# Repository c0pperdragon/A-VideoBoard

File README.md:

# A-Video Board

A small FPGA board with a component video interface to directly drive
an analog monitor or TV input.
Its main purpose is to create component video / RGB mods of vintage
home computers and consoles or to provide video output for hobby projects.

It consists of the purest minimum parts necessary to have a multi-purpose
FPGA combined with a simple way to generate a YPbPr signal. After much research
I finally settled on a cheap MAX 10 device in a TQFP-144 package which I can 
solder by hand (barely). The rest of the parts are pretty cheap and quite easy to solder. 

To interface any of the vintage systems to the A-Video Board, level shifters
are necessary to translate the 5 volt to 3.3 volt for the FPGA input pins. These level
shifters can be implemented in a system specific daughter board that can be stacked
on top of the A-Video board. Any such interface board can probably be implemented in a 
simple single-sided wide-pitch PCB that can be even home-etched with some experience.

Currently I have built applications of the A-Video board for 
* [Commodore 64](/c64mod)
* [Atari 8 bit machines](/atarimod)
* [ZX Spectrum](/zxspectrummod)

## Images

## Board design

The board has these main parts

* 10M02SCE144: fairly cheap FPGA of the MAX10 series
* LM1117IMPX-3.3:   linear voltage regulator
* LFSPX0024957:     25Mhz clock generator
* THS7316:          video output amplifier
* R1-R19:           three 5-bit DACs made from transistors

and various supporting passive components, mainly decoupling, filtering and pull-ups.

It has the following connectors:
* GPIO1  20-pin header that directly connects to FPGA pins
* GPIO2  10-pin header with two pins providing GND and +3.3V, the remaining 8 connect to the FPGA.
* JTAG   10-pin header for programming the FPGA (via an USB-Blaster or compatible device)
* 3 RCA sockets to output the video signal (normally YPbPr, but other formats could be produced as well).
 Note that in the schematics these sockets are denoted as BNC, but are actually RCA connectors of type 
 RCJ-046 (green), RCJ-042 (red), RCJ-045 (blue).
* GND, VIN  Provide between 4.5V and 9V as supply voltage. The board consumes about 80mA.
 
## Contact
If you plan to use an A-Video board, feel free to contact me for assistance:
reinhard.grafl (at) aon.at  
Maybe I will either have some spare PCBs I could send you to populate yourself,
or even provide you with a fully assembled board for the cost of the parts and shipping.

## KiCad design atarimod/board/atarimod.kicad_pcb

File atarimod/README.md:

# Atari RGB Mod

Built on the A-Video board, this is a modification usable for Atari 8-bit 
computers that generate YPbPr signal in either 288p or 576p to display on
modern displays. 

## Motivation

These old Atari computers generate the colour output signal directly in the weird way that was
necessary to construct a PAL or NTSC signal. The technique is called "quadrature amplitude modulation" and has the
disadvantage of not being completely reversible, so the original colours can not be reconstructed from this
signal.
Even worse, the XL line of machines does not even provide this signal directly on the video output, but
only already combined with the luminance signal as composite video. There are simple ways to provide 
separate luminance and colour, but even then the quality is pretty bad. 
This was not such a problem on cathode ray tube (CRT) displays, but on modern LCD TVs this signal looks totally
unusable.

So, no matter how I tried, I could not reliably re-construct the original colours from the colour signal output. 
The only way to really solve the issue was to intercept the necessary information in digital form to 
create a perfectly sharp and clear analog video signal by my own circuitry. 

## Theory of Operation

The FPGA chip passively listens to all relevant pins of the GTIA graphics chip and re-implements the 
relevant logic of the GTIA in its logic fabric, effectively providing a second GTIA (parts of it).
To sniff the signals from the GTIA, a specific adapter board is needed that sits between the 
GTIA and its socket. Revision 3 of the adapter is now pretty small and should fit in all Atari models.
From this adapter, a 20-pin ribbon cable (either mounted permanently to the adapter or using a plug)
leads to the FPGA board.
This FPGA board can either be the generic A-Video board or a re-purposed C64 Video Enhancement Board. 
Both boards are firmeware-compatible, but differ in their size and connector options. You should 
also be able to fairly easily change these connectivity options anyway.

## Adapter building details (Rev. 3)

In the doc folder, there are schematics, gerber files and a bill of material to build the adapter.
Ideally you need a 0.8mm PCB (a slighly thicker boards will also work) and assemble everything except
the P1 socket.  This specific socket is meant to be put into the big holes, so the extra-long solder tails 
will stick out pretty far on the bottom side. These will then fit into the IC socket on the Atari.
Take care not to get any solder onto these thin tails when soldering the ticker barrels into the 
adapter board (this can become tricky, but with a 0.8mm board it should not be too hard).
Before actually soldering the socket you have to cut away one of the plastic cross-beams so it
will not conflict with the ICs.

For attaching the 20-pin ribbon cable to P2, you have several options. I used an angled 
pin-header with a standard ribbon cable connector to keep a low profile. If there is space 
in your device you can as well use a straight pain-header. An even more sophisticated option
is a permantent PCB-to-ribbon-cable header which can be found with quite a low profile.
You can even solder the ribbon cable wires direcly into the board or whatever you fancy.

## FPGA Details

The FPGA on the A-Video board is programmed in VHDL, using the free version of the Quartus II development suite.
This chip has an on-board non-volatile program memory, so no external flash is needed and the chip has
a very short start-up time. There is a PLL built in which I use to generate a 228Mhz clock from the 25Mhz reference.
With this 228Mhz and some advanced  programming I can multiply the Atari pixel clock to a pretty clean (below 1 ns jitter) 14,1875 MHz clock to drive the whole circuit and create a nice output signal.

On non-PAL machines the Atari pixel clock runs at a slightly different speed. There the clock multiplier circuit will actually produce an internal clock that has variations in their clock cycle length. This will lead
to a slightly different length of every other pixel in 240p mode, and of every 4th pixel in 480p mode.

## Output

The mod can be used to create three different output formats:
* 240p/288p  (default)
* 480p/576p
* 480p/576p with scanline effect 

Selecting the output can be done by jumper connectors or an external switch (already provided 
in the C64 Video Enhancement):
* Connect GPIO2_4 to GND: 480p/576p
* Connect GPIO2_5 or GPIO2_6 to GND: 480p/576p with scanline effect

## Images
")

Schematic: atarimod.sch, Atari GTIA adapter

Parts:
C1, C2: 10uF; C_0805_2012Metric_Pad1.15x1.40mm_HandSolder
C3, C4, C5, C6: 100nF; C_0603_1608Metric_Pad1.05x0.95mm_HandSolder
IC1, IC2, IC3, IC4: SN74LVC14ADBR; SSOP-14_5.3x6.2mm_P0.65mm
P1: DIP40_Socket; socket_embedded_40pin
P2: CONN_02X10; PinHeader_2x10_P2.54mm_Vertical
R10: 100; R_0805_2012Metric_Pad1.15x1.40mm_HandSolder
U2: MIC5504-3.3YM5; SOT-23-5

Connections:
+3V3: C2.1, C3.2, C4.2, C5.2, C6.2, IC1.14, IC2.14, IC3.14, IC4.14, U2.5
+5V: C1.1, P1.27, U2.1, U2.3
A0: IC1.4, P2.3
A1: IC1.2, P2.1
A2: IC1.12, P2.2
A3: IC1.10, P2.4
A4: IC1.8, P2.6
AN0: IC4.2, P2.13
AN1: IC4.4, P2.15
AN2: IC4.6, P2.17
CLK: IC4.12, R10.2
CS: IC3.8, P2.18
D0: IC3.2, P2.11
D1: IC2.6, P2.9
D2: IC2.4, P2.7
D3: IC2.2, P2.5
D4: IC2.12, P2.8
D5: IC2.10, P2.10
D6: IC2.8, P2.12
D7: IC3.12, P2.14
GND: C1.2, C2.2, C3.1, C4.1, C5.1, C6.1, IC1.5, IC1.7, IC2.7, IC3.3, IC3.5, IC3.7, IC4.7, IC4.9, P1.3, U2.2
HALT: IC4.10, P2.20
unnamed: IC1.1, P1.1
unnamed: IC1.3, P1.2
unnamed: IC1.9, P1.38
unnamed: IC1.11, P1.39
unnamed: IC1.13, P1.40
unnamed: IC2.1, P1.4
unnamed: IC2.3, P1.5
unnamed: IC2.5, P1.6
unnamed: IC2.9, P1.35
unnamed: IC2.11, P1.36
unnamed: IC2.13, P1.37
unnamed: IC3.1, P1.7
unnamed: IC3.9, P1.32
unnamed: IC3.11, P1.33
unnamed: IC3.13, P1.34
unnamed: IC4.1, P1.18
unnamed: IC4.3, P1.19
unnamed: IC4.5, P1.20
unnamed: IC4.11, P1.26
unnamed: IC4.13, P1.29
unnamed: P2.19, R10.1
RW: IC3.10, P2.16

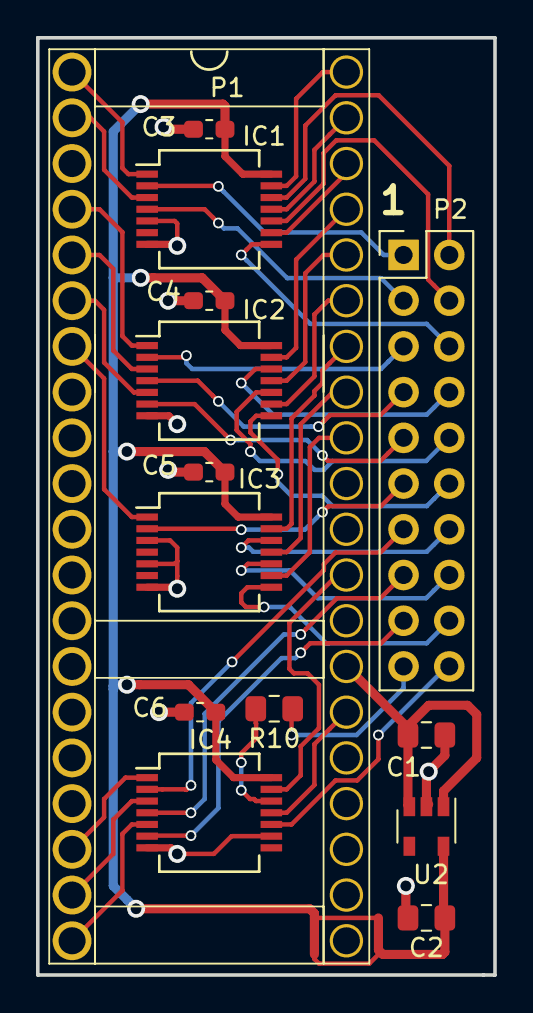
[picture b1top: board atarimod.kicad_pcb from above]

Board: 2 copper layers, 25.4 x 52.1 mm, 14 parts (0 on the bottom side), 44 nets.

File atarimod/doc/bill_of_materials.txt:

References       Type                                                 Value/Part Number      Size

C1,C2            Ceramic Capacitor                                    1 uF                   2012 metric
C3,C4,C5,C6      Ceramic Capacitor                                    100 nF                 1608 metric
IC1,IC2,IC3,IC4  Schmitt-Trigger Inverter                             SN74LVC14ADBR          SSOP-14
P1               40-pin IC precision socket with long solder tails    111-93-640-41-001000   DIP 40
P2               Pinheader/Ribbon cable connector                     any                    2x20, 2.54mm 
R10              SMD Resistor                                         100 ohm                2012 metric
U2               LDO Voltage Regulator 3.3V                           MIC5504-3.3YM5         SOT-23-5

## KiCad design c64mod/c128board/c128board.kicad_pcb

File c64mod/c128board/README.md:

# C128 adapter

This is an adapater to be plugged between the VIC-IIe and its socket in a Commodore 128.
Using this the, C64 Video Enchancement Board should in theory be able to work for the 40 columns mode 
display of the C128.

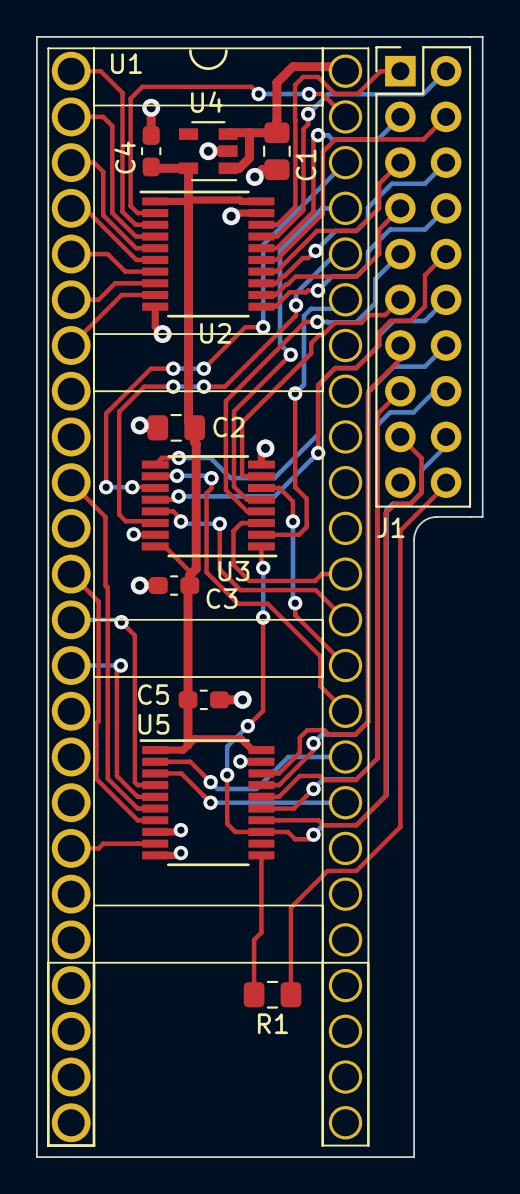
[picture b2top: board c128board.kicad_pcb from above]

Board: 2 copper layers, 24.8 x 62.2 mm, 12 parts (0 on the bottom side), 46 nets.

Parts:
C1, C2: 10uF; C_0805_2012Metric_Pad1.15x1.40mm_HandSolder
C3, C4, C5: 100nF; C_0603_1608Metric_Pad1.05x0.95mm_HandSolder
J1: Conn_02x10_Odd_Even; PinHeader_2x10_P2.54mm_Vertical
R1: 100Ohm; R_0805_2012Metric_Pad1.15x1.40mm_HandSolder
U1: VIC-IIe; socket_embedded_48pin
U2: MIC5504-3.3YM5; SOT-23-5
U3: LVC257; TSSOP-16_4.4x5mm_P0.65mm
U4, U5: LVC245; TSSOP-20_4.4x6.5mm_P0.65mm

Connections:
+3V3: C2.1, C3.1, C4.1, C5.1, U2.5, U3.16, U4.1, U4.20, U5.1, U5.20
+5V: C1.1, U1.48, U2.1, U2.3
A0: J1.14, U5.17
A1: J1.13, U5.18
AEC: J1.18, U3.1, U5.13
BA: J1.17, U5.14
CS: J1.15, U5.16
DB0: J1.8, U4.11
DB1: J1.7, U4.12
DB2: J1.6, U4.13
DB3: J1.5, U4.14
DB4: J1.4, U4.15
DB5: J1.3, U4.16
DB6: J1.2, U4.17
DB7: J1.1, U4.18
DB8_A2: J1.12, U3.9
DB9_A3: J1.11, U3.7
DB10_A4: J1.10, U3.12
DB11_A5: J1.9, U3.4
GND: C1.2, C2.2, C3.2, C4.2, C5.2, J1.19, U1.24, U2.2, U3.8, U3.15, U4.10, U4.19, U5.8, U5.10, U5.19
unnamed: R1.2, U5.11
unnamed: U1.1, U4.3
unnamed: U1.2, U4.4
unnamed: U1.3, U4.5
unnamed: U1.4, U4.6
unnamed: U1.5, U4.7
unnamed: U1.6, U4.8
unnamed: U1.7, U4.9
unnamed: U1.10, U5.6
unnamed: U1.12, U5.7
unnamed: U1.13, U5.4
unnamed: U1.14, U5.5
unnamed: U1.18, U5.9
unnamed: U1.32, U5.3
unnamed: U1.33, U5.2
unnamed: U1.34, U3.10
unnamed: U1.35, U3.6
unnamed: U1.36, U3.13
unnamed: U1.37, U3.3
unnamed: U1.43, U3.2
unnamed: U1.44, U3.14
unnamed: U1.45, U3.5
unnamed: U1.46, U3.11
unnamed: U1.47, U4.2
PHI0: J1.20, R1.1
RW: J1.16, U5.15

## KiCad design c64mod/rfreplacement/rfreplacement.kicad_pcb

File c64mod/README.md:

# C64 RGB Mod

Built on the A-Video board, this is a modification usable for the Commodore 64 computer
that generates a YPbPr signal in either 288p or 576p to display on modern displays.

## Motivation

I wanted to get the most perfect display from an original C64 computer. After many failed attempts to 
reconstruct a digitally perfect pixel-by-pixel display from the S-Video output, I finally came back
to my original idea to emulate the inner workings of the VIC-II chip. 
So, as for the atari 8-bit line and the ZX Spectrum, I applied my trusty A-Video board. 

## Building details

The FPGA chip passively listens to all relevant pins of the VIC graphics chip and re-implements the 
relevant logic of the GTIA in its logic fabric, effectively providing a second VIC (parts of it).
The mod board consists of two parts: A small adapter board that sits under the VIC and sniffs all relevant
pins, and the A-Video board that does the actual processing. The 5 volt signals from the C64 are
level-shifted by the adapter board down to 3.3 volts for use by the FPGA.
Since the adapter board only listens to the signals (with very high-impedience input pins), it 
will not influence the working of the VIC or any other part of the system in any way. The FPGA implementation
may have some glitches, but this should only affect the visual output.
Note that the mod consumes an additional 100mA of current from the 5 volt rail, 
so make sure that your power supply can handle this.

## Assembling the VIC adapter board

If you want to build your own adapter board, you need to have a PCB manufactured with 0.8mm thickness 
(use the gerber.zip for ordering). After soldering the ICs and passives, you need to fit a 40-pin
IC socket into the big holes. Use the socket type with round pins (the more expensive ones).
Solder from below and remove as much excess solder as possible. Then install the ribbon cable connector.
Take special care when installing the voltage regulator, as this small package always gave me the most trouble.
For your convenience, I have set up a [BOM](doc/adapterboard_bom.ods) and a parts list at 
[mouser](https://www.mouser.com/ProjectManager/ProjectDetail.aspx?AccessID=2b75b16750)
containing everything to build the board.

## Connectors

In my current build, the A-Video port is just screwed on top of the existing RF modulator.
This saved me the trouble of removing the modulator first (which would need additional circuitry to
keep the A/V output working). But this comes at the cost that the back of the computer case 
now has a rather large and ugly hole. I am pretty sure there are good solutions available to get rid of
this big modulator box while keeping the A/V functionality. Then the YPbPr connectors would be located
much lower and would look more natural.
If you even want a totally reversible mod you could probably place the A-Video board somewhere inside the
case and bring out the YPbPr cable through the user port opening.

## Output

The mod can be used to create three different output formats:
* 288p (default)
* 576p
* 576p with scanline effect

Selecting the output can be done by jumper connectors or an external switch:
* Connect GPIO2_4 to GPIO2_2 (GND): 576p
* Connect GPIO2_6 to GPIO2_2 (GND): 576p with scanline effect

## Images

")

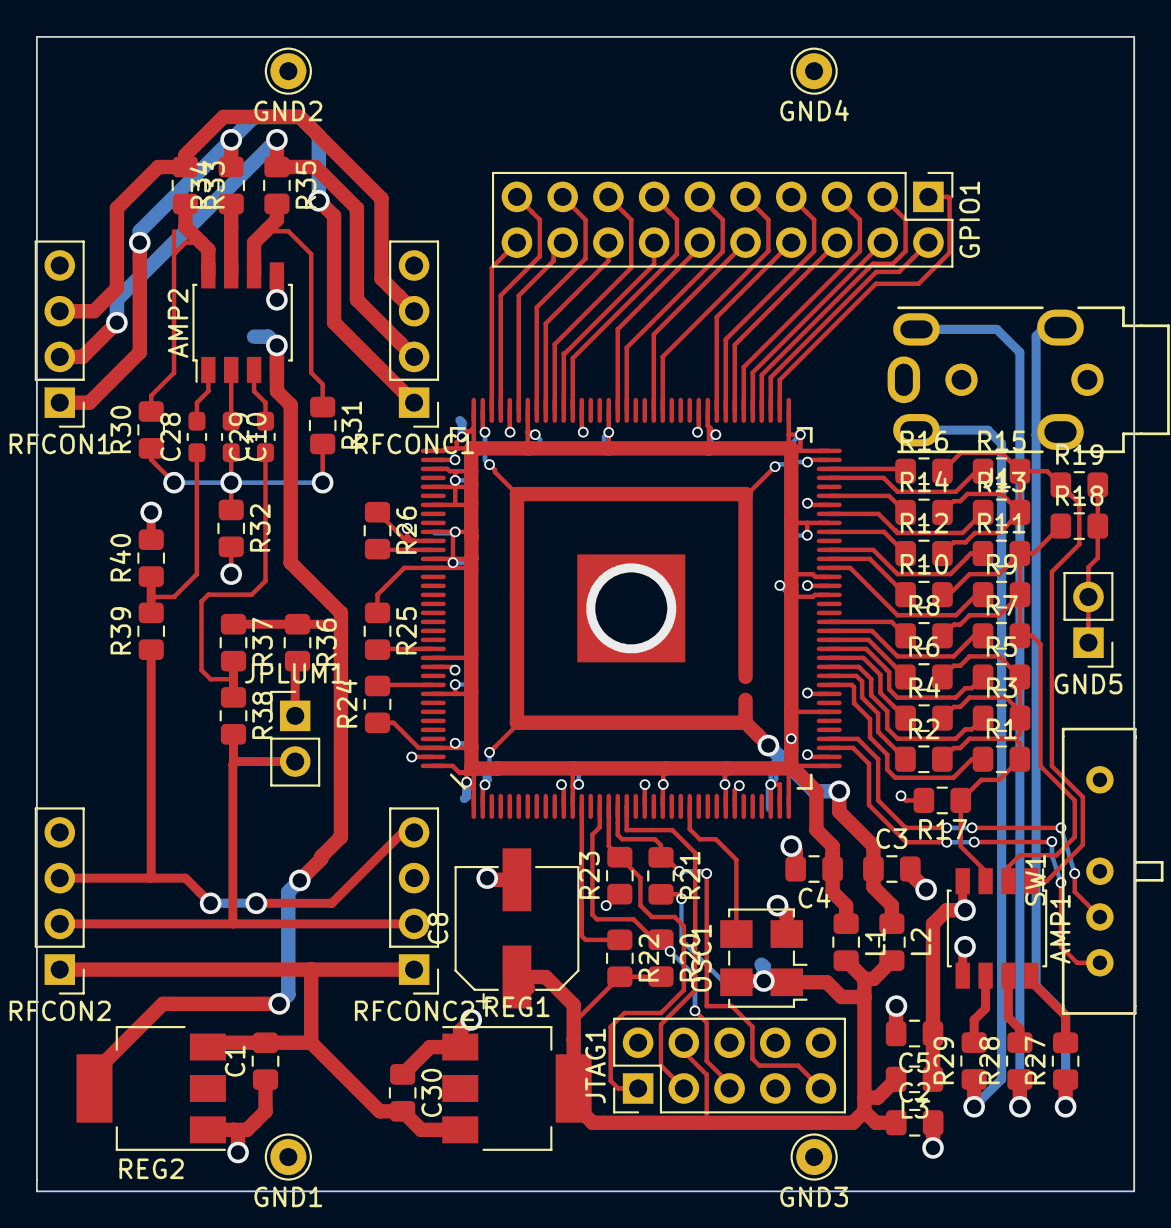
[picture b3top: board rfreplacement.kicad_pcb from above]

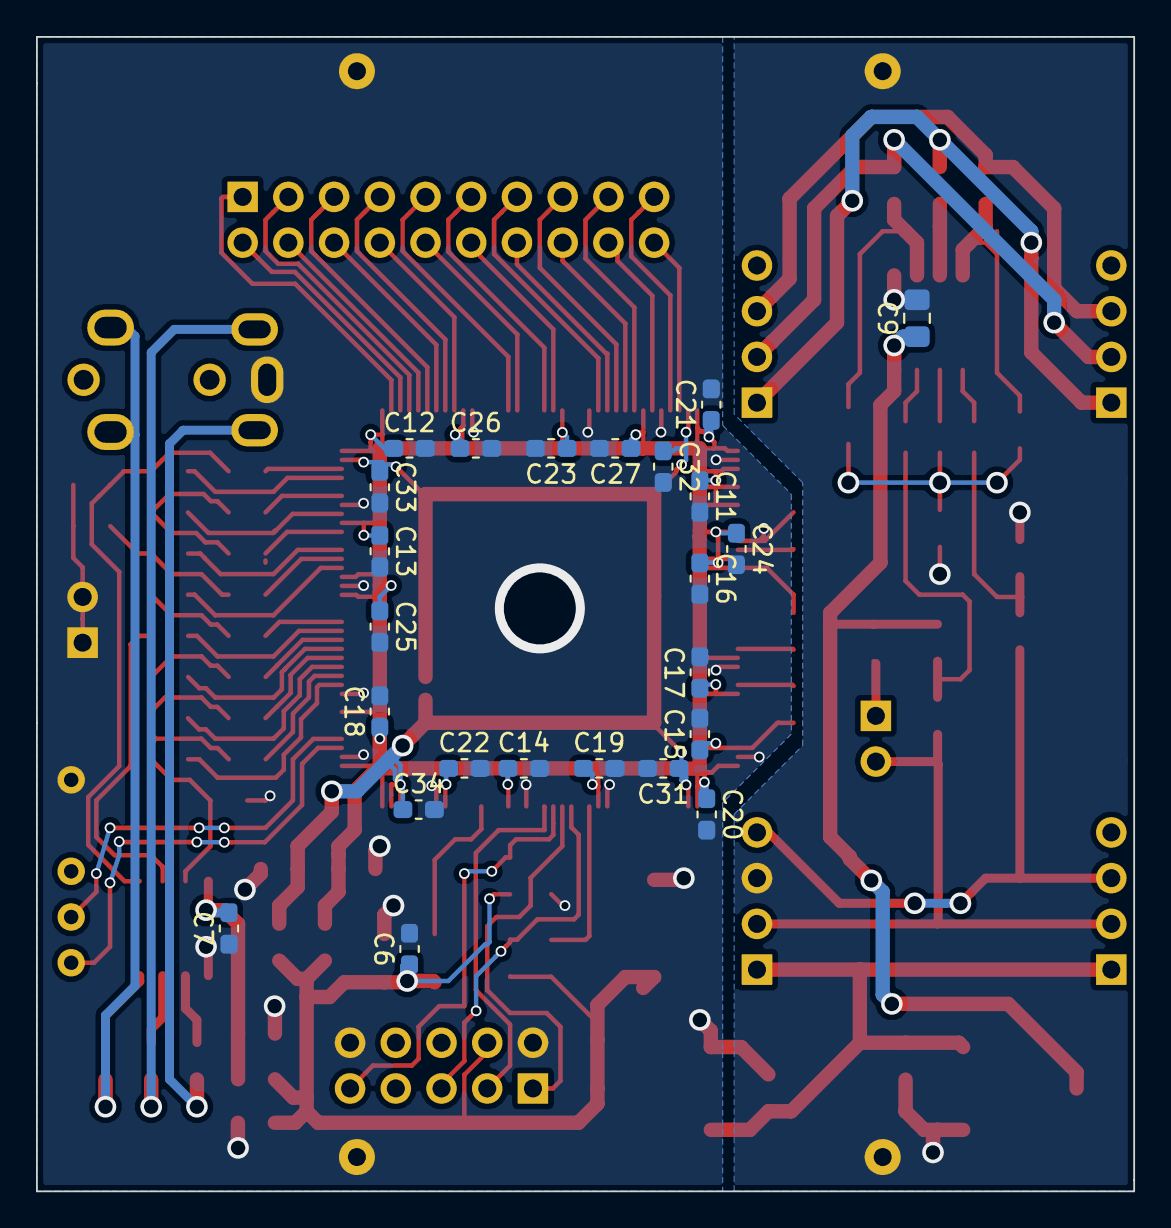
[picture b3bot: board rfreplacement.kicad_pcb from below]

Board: 2 copper layers, 61.0 x 64.1 mm, 97 parts (24 on the bottom side), 79 nets.

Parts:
AMP1, AMP2: THS7316; SSOP-8_3.95x5.21x3.27mm_P1.27mm
C1, C2, C3, C4, C5, C9, C30: 10uF; C_0805_2012Metric_Pad1.15x1.40mm_HandSolder
C6, C7, C10, C11, C12, C13, C14, C15, C16, C17, C18, C19, C20, C21, C22, C23, C24, C25, C26, C27, C28, C29, C31, C32, C33, C34: 100nF; C_0603_1608Metric_Pad1.05x0.95mm_HandSolder
C8: 100uF; CP_Elec_6.3x5.8
GND1, GND2, GND3, GND4: Conn_01x01; Pin_D1.0mm_L10.0mm
GND5: Conn_01x02; PinHeader_1x02_P2.54mm_Vertical
GPIO1: Conn_02x10_Odd_Even; PinHeader_2x10_P2.54mm_Vertical
J1: AudioJack4_Ground; Conrad 4pin audio jack
JPLUM1: Jumper_2_Open; PinHeader_1x02_P2.54mm_Vertical
JTAG1: Conn_02x05_Odd_Even; PinHeader_2x05_P2.54mm_Vertical
L1, L2, L3: 10uH; L_0805_2012Metric_Pad1.15x1.40mm_HandSolder
OSC1: LFSPXO024957; Oscillator_SMD_EuroQuartz_XO53-4Pin_5.0x3.2mm_HandSoldering
R1: 1k1; R_0805_2012Metric_Pad1.15x1.40mm_HandSolder
R2, R7, R12, R31: 1k; R_0805_2012Metric_Pad1.15x1.40mm_HandSolder
R3, R8, R13: 2k; R_0805_2012Metric_Pad1.15x1.40mm_HandSolder
R4, R9, R14: 4k; R_0805_2012Metric_Pad1.15x1.40mm_HandSolder
R5, R10, R15: 8k; R_0805_2012Metric_Pad1.15x1.40mm_HandSolder
R6, R11, R16: 16k; R_0805_2012Metric_Pad1.15x1.40mm_HandSolder
R17, R18, R19: 150; R_0805_2012Metric_Pad1.15x1.40mm_HandSolder
R20, R21, R22, R23, R24, R25, R26: 10k; R_0805_2012Metric_Pad1.15x1.40mm_HandSolder
R27, R28, R29, R33, R34, R35: 75; R_0805_2012Metric_Pad1.15x1.40mm_HandSolder
R30: 3k3; R_0805_2012Metric_Pad1.15x1.40mm_HandSolder
R32: 2k2; R_0805_2012Metric_Pad1.15x1.40mm_HandSolder
R36, R38, R39: 680; R_0805_2012Metric_Pad1.15x1.40mm_HandSolder
R37, R40: 330; R_0805_2012Metric_Pad1.15x1.40mm_HandSolder
REG1, REG2: LM1117IMPX-3.3; SOT-223
RFCON1, RFCON2: Conn_01x04; PinHeader_1x04_P2.54mm_Vertical
RFCONC1, RFCONC2: Conn_01x04; PinHeader_1x04_P2.54mm_Vertical
SW1: SW_SP3T; slider
U2: 10M02SCE144; QFP_144_GND

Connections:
+12V: C1.2, C30.2, REG1.3, REG2.3, RFCON2.1, RFCONC2.1
/3V3A: C2.1, C6.1, C8.1, JTAG1.4, L1.2, L2.2, L3.2, OSC1.1, OSC1.4, R20.2, R21.2, R22.2, REG1.4
/3V3B: C4.1, C11.1, C12.1, C13.1, C14.1, C15.1, C16.1, C17.1, C18.1, C19.1, C20.1, C21.1, C22.1, C23.1, C24.1, C25.1, C26.1, C27.1, L1.1, R24.1, R25.1, U2.1, U2.12, U2.22, U2.29, U2.36, U2.37, U2.43, U2.56, U2.58, U2.64, U2.72, U2.73, U2.82, U2.93, U2.102, U2.108, U2.109, U2.111, U2.113, U2.115, U2.118, U2.121, U2.122, U2.132, U2.136, U2.142, U2.144
/3V3C: C3.1, C31.1, C32.1, C33.1, C34.1, L2.1, U2.2, U2.34, U2.35, U2.71, U2.107
/3V3D: AMP1.4, C5.1, C7.2, L3.1
/3V3X: AMP2.4, C9.1, R36.1, R37.1, REG2.4
/CHROMA_IN: R39.1, RFCON2.3, RFCONC2.4
/CHROMA_OUT: R33.1, RFCON1.3, RFCONC1.3
/COMPOSITE_OUT: R34.2, RFCON1.1, RFCONC1.1
/LUMA_IN: JPLUM1.2, R38.2, RFCON2.2, RFCONC2.2
/LUMA_OUT: R35.1, RFCON1.2, RFCONC1.2
/PB: J1.R1, R28.1
/PB1: AMP1.7, R28.2
/PR: J1.T, R27.1
/PR1: AMP1.8, R27.2
/PY1: AMP1.6, R29.2
/Y: J1.R2, R29.1
GND: AMP1.5, C2.2, C3.2, C4.2, C5.2, C6.2, C7.1, C8.2, C11.2, C12.2, C13.2, C14.2, C15.2, C16.2, C17.2, C18.2, C19.2, C20.2, C21.2, C22.2, C23.2, C24.2, C25.2, C26.2, C27.2, C30.1, C31.2, C32.2, C33.2, C34.2, GND3.1, GND4.1, GND5.1, GND5.2, J1.S, JTAG1.2, JTAG1.10, OSC1.2, R17.2, R18.2, R19.2, R23.1, R26.1, REG1.1, SW1.3, U2.11, U2.20, U2.30, U2.38, U2.45, U2.57, U2.66, U2.83, U2.96, U2.104, U2.110, U2.119, U2.133, U2.143, U2.145
GNDA: AMP2.5, C1.1, C9.2, GND1.1, GND2.1, R32.2, R40.2, REG2.1, RFCONC2.3
unnamed: AMP1.1, R12.2, R13.2, R14.2, R15.2, R16.2, R19.1
unnamed: AMP1.2, R7.2, R8.2, R9.2, R10.2, R11.2, R18.1
unnamed: AMP1.3, R1.2, R2.2, R3.2, R4.2, R5.2, R6.2, R17.1
unnamed: AMP2.1, C28.2
unnamed: AMP2.2, C10.1
unnamed: AMP2.3, C29.2
unnamed: AMP2.6, R31.1, R35.2
unnamed: AMP2.7, R34.1
unnamed: AMP2.8, R30.2, R33.2
unnamed: C10.2, R30.1, R31.2, R32.1
unnamed: C28.1, R39.2, R40.1
unnamed: C29.1, R37.2, R38.1
unnamed: GPIO1.1, U2.74
unnamed: GPIO1.2, U2.75
unnamed: GPIO1.3, U2.76
unnamed: GPIO1.4, U2.77
unnamed: GPIO1.5, U2.78
unnamed: GPIO1.6, U2.79
unnamed: GPIO1.7, U2.80
unnamed: GPIO1.8, U2.81
unnamed: GPIO1.9, U2.87
unnamed: GPIO1.10, U2.88
unnamed: GPIO1.11, U2.91
unnamed: GPIO1.12, U2.92
unnamed: GPIO1.13, U2.97
unnamed: GPIO1.14, U2.98
unnamed: GPIO1.15, U2.99
unnamed: GPIO1.16, U2.100
unnamed: GPIO1.17, U2.101
unnamed: GPIO1.18, U2.103
unnamed: GPIO1.19, U2.105
unnamed: GPIO1.20, U2.106
unnamed: JPLUM1.1, R36.2
unnamed: JTAG1.1, R23.2, U2.16
unnamed: JTAG1.3, U2.18
unnamed: JTAG1.5, R20.1, U2.15
unnamed: JTAG1.9, R21.1, U2.17
unnamed: OSC1.3, U2.25
unnamed: R1.1, U2.46
unnamed: R2.1, U2.47
unnamed: R3.1, U2.48
unnamed: R4.1, U2.49
unnamed: R5.1, U2.50
unnamed: R6.1, U2.51
unnamed: R7.1, U2.52
unnamed: R8.1, U2.53
unnamed: R9.1, U2.59
unnamed: R10.1, U2.60
unnamed: R11.1, U2.61
unnamed: R12.1, U2.63
unnamed: R13.1, U2.65
unnamed: R14.1, U2.67
unnamed: R15.1, U2.69
unnamed: R16.1, U2.70
unnamed: R22.1, U2.13
unnamed: R24.2, U2.135
unnamed: R25.2, U2.131
unnamed: R26.2, U2.120
unnamed: SW1.1, U2.39
unnamed: SW1.2, U2.40

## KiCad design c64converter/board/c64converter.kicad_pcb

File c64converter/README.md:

# C64 to YPbPr converter

Instead of designing a modification for the C64, I will try to somehow
build a device that receives the luma and chroma signals from the C64 
A/V output and generates a clean YPbPr signal from it. While there are 
quite some generic S-Video to RGB converters around, none can generate a picture
as clean as should be possible for a dedicated solution.

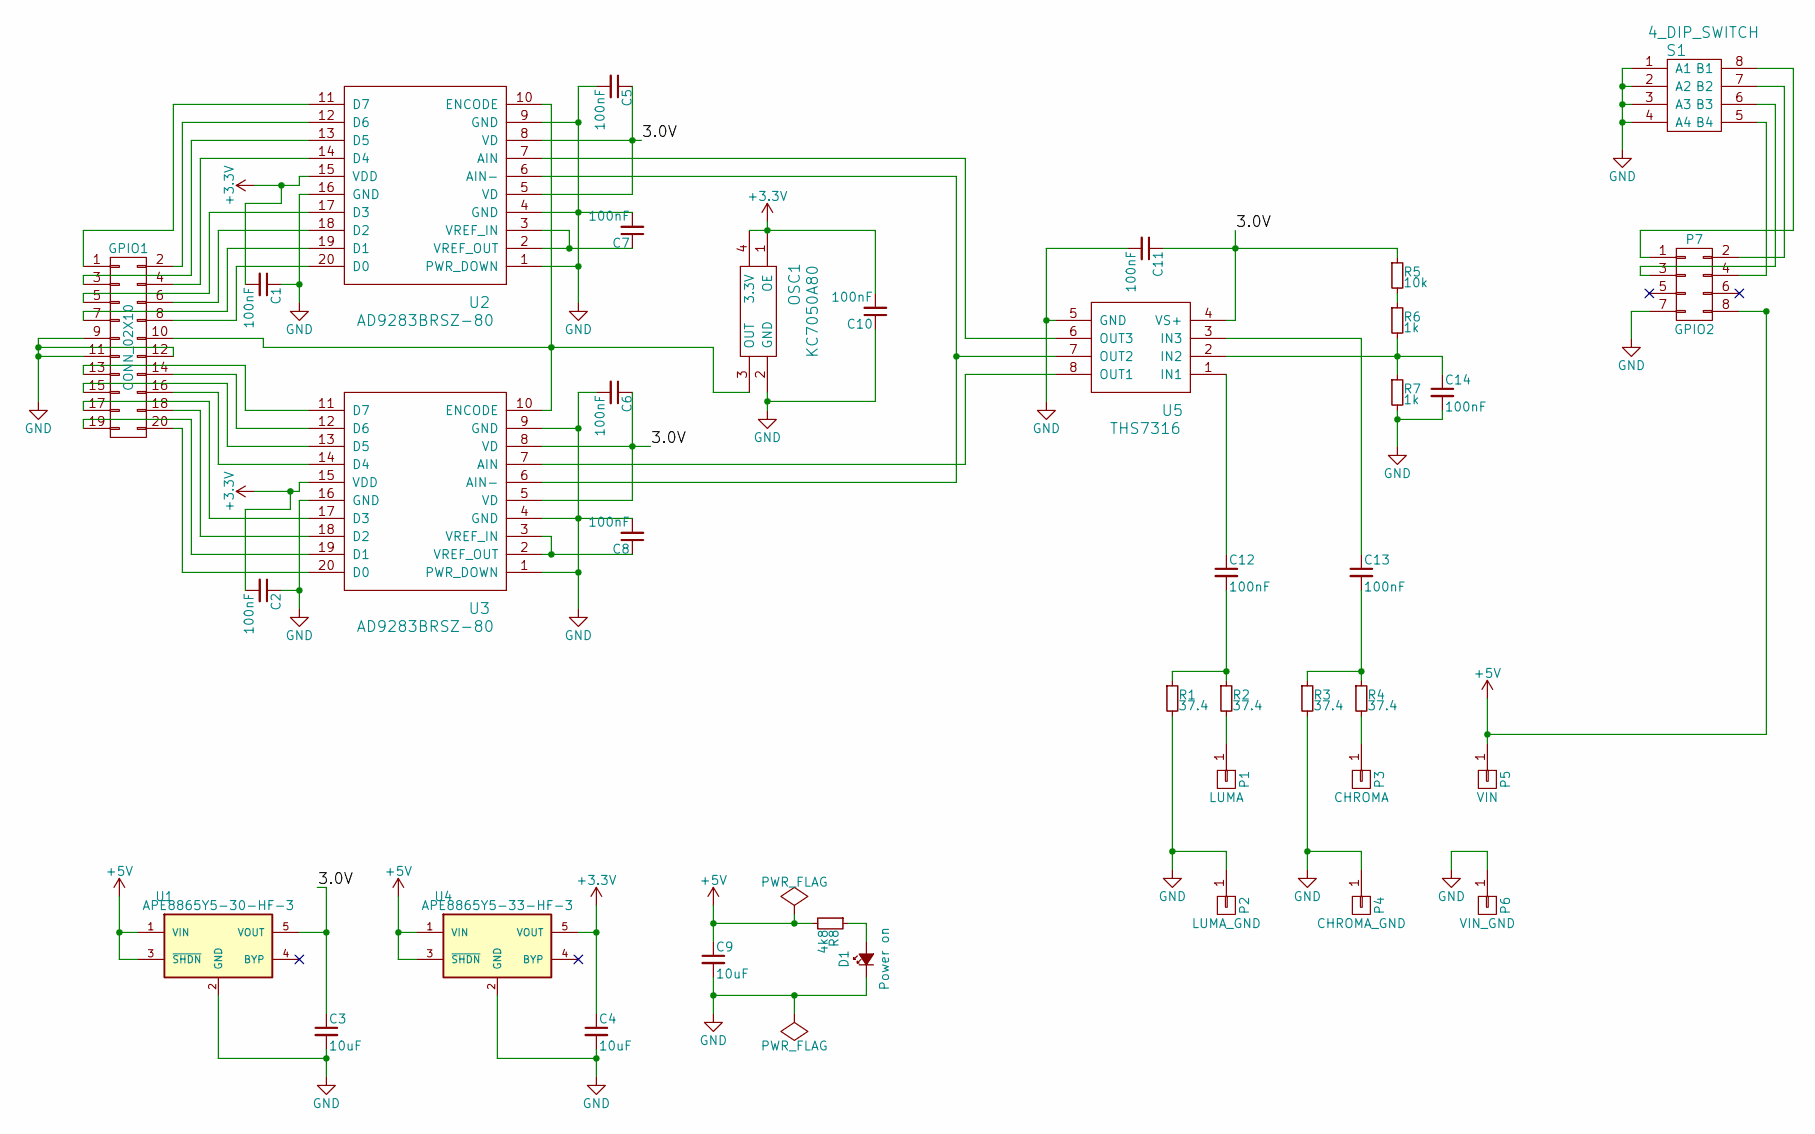
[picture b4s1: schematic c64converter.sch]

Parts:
C1, C2, C5, C6, C7, C8, C10, C11, C12, C13, C14: 100nF; C_0603_HandSoldering
C3, C4, C9: 10uF; C_0805_HandSoldering
D1: Power on; LED_D3.0mm
GPIO1: CONN_02X10; Socket_Strip_Straight_2x10_Pitch2.54mm
OSC1: KC7050A80; Oscillator_SMD_EuroQuartz_XO53-4pin_5.0x3.2mm_HandSoldering
P1: LUMA; SolderWirePad_single_1mmDrill
P2: LUMA_GND; SolderWirePad_single_1-5mmDrill
P3: CHROMA; SolderWirePad_single_1mmDrill
P4: CHROMA_GND; SolderWirePad_single_1-5mmDrill
P5: VIN; SolderWirePad_single_1mmDrill
P6: VIN_GND; SolderWirePad_single_1-5mmDrill
P7: GPIO2; Socket_Strip_Straight_2x04_Pitch2.54mm
R1, R2, R3, R4: 37.4; R_0805_HandSoldering
R5: 10k; R_0805_HandSoldering
R6, R7: 1k; R_0805_HandSoldering
R8: 4k8; R_0805_HandSoldering
S1: 4_DIP_SWITCH; DIP-8_W7.62mm_LongPads
U1: APE8865Y5-30-HF-3; SOT-23-5
U2, U3: AD9283BRSZ-80; SSOP-20_5.3x7.2mm_Pitch0.65mm
U4: APE8865Y5-33-HF-3; SOT-23-5
U5: THS7316; SOIC-8_3.9x4.9mm_Pitch1.27mm

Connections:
+3V3: C1.2, C2.2, C4.1, C10.2, OSC1.1 (OE), OSC1.4 (3.3V), U2.15 (VDD), U3.15 (VDD), U4.5 (VOUT)
+5V: C9.1, P5.1, P7.8, R8.2, U1.1 (VIN), U1.3 (~SHDN~), U4.1 (VIN), U4.3 (~SHDN~)
/3.0V: C3.1, C5.1, C6.1, C11.1, R5.1, U1.5 (VOUT), U2.5 (VD), U2.8 (VD), U3.5 (VD), U3.8 (VD), U5.4 (VS+)
GND: C1.1, C2.1, C3.2, C4.2, C5.2, C6.2, C7.2, C8.2, C9.2, C10.1, C11.2, C14.2, D1.1 (K), GPIO1.9, GPIO1.11, GPIO1.12, OSC1.2 (GND), P2.1, P4.1, P6.1, P7.7, R1.2, R3.2, R7.2, S1.1 (A1), S1.2 (A2), S1.3 (A3), S1.4 (A4), U1.2 (GND), U2.1 (PWR_DOWN), U2.4 (GND), U2.9 (GND), U2.16 (GND), U3.1 (PWR_DOWN), U3.4 (GND), U3.9 (GND), U3.16 (GND), U4.2 (GND), U5.5 (GND)
unnamed: C7.1, U2.2 (VREF_OUT), U2.3 (VREF_IN)
unnamed: C8.1, U3.2 (VREF_OUT), U3.3 (VREF_IN)
unnamed: C12.1, U5.1 (IN1)
unnamed: C12.2, R1.1, R2.1
unnamed: C13.1, U5.3 (IN3)
unnamed: C13.2, R3.1, R4.1
unnamed: C14.1, R6.2, R7.1, U5.2 (IN2)
unnamed: D1.2 (A), R8.1
unnamed: GPIO1.1, U2.11 (D7)
unnamed: GPIO1.2, U2.12 (D6)
unnamed: GPIO1.3, U2.13 (D5)
unnamed: GPIO1.4, U2.14 (D4)
unnamed: GPIO1.5, U2.17 (D3)
unnamed: GPIO1.6, U2.18 (D2)
unnamed: GPIO1.7, U2.19 (D1)
unnamed: GPIO1.8, U2.20 (D0)
unnamed: GPIO1.10, OSC1.3 (OUT), U2.10 (ENCODE), U3.10 (ENCODE)
unnamed: GPIO1.13, U3.11 (D7)
unnamed: GPIO1.14, U3.12 (D6)
unnamed: GPIO1.15, U3.13 (D5)
unnamed: GPIO1.16, U3.14 (D4)
unnamed: GPIO1.17, U3.17 (D3)
unnamed: GPIO1.18, U3.18 (D2)
unnamed: GPIO1.19, U3.19 (D1)
unnamed: GPIO1.20, U3.20 (D0)
unnamed: P1.1, R2.2
unnamed: P3.1, R4.2
unnamed: P7.1, S1.8 (B1)
unnamed: P7.2, S1.7 (B2)
unnamed: P7.3, S1.6 (B3)
unnamed: P7.4, S1.5 (B4)
unnamed: R5.2, R6.1
unnamed: U2.6 (AIN-), U3.6 (AIN-), U5.7 (OUT2)
unnamed: U2.7 (AIN), U5.6 (OUT3)
unnamed: U3.7 (AIN), U5.8 (OUT1)

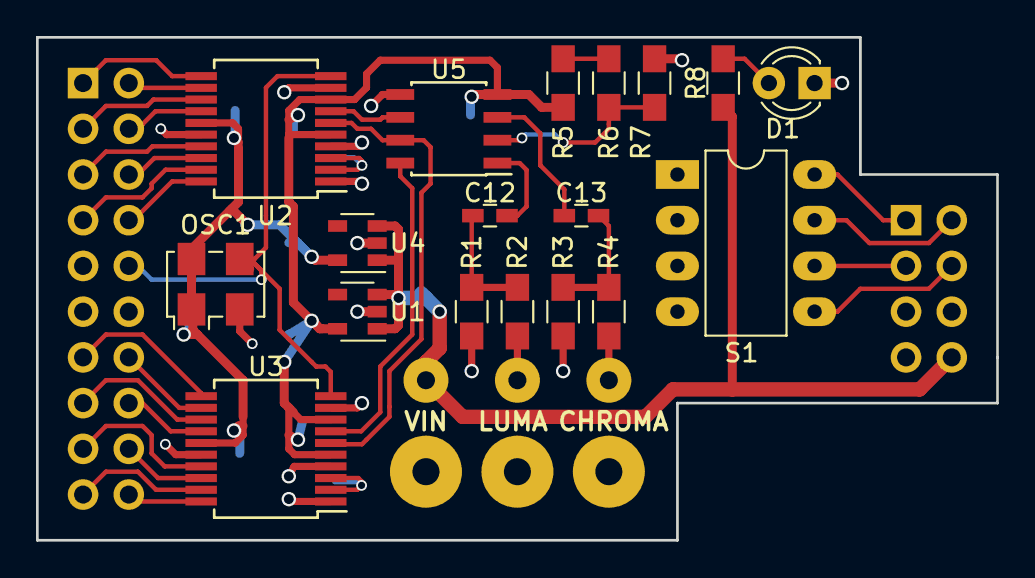
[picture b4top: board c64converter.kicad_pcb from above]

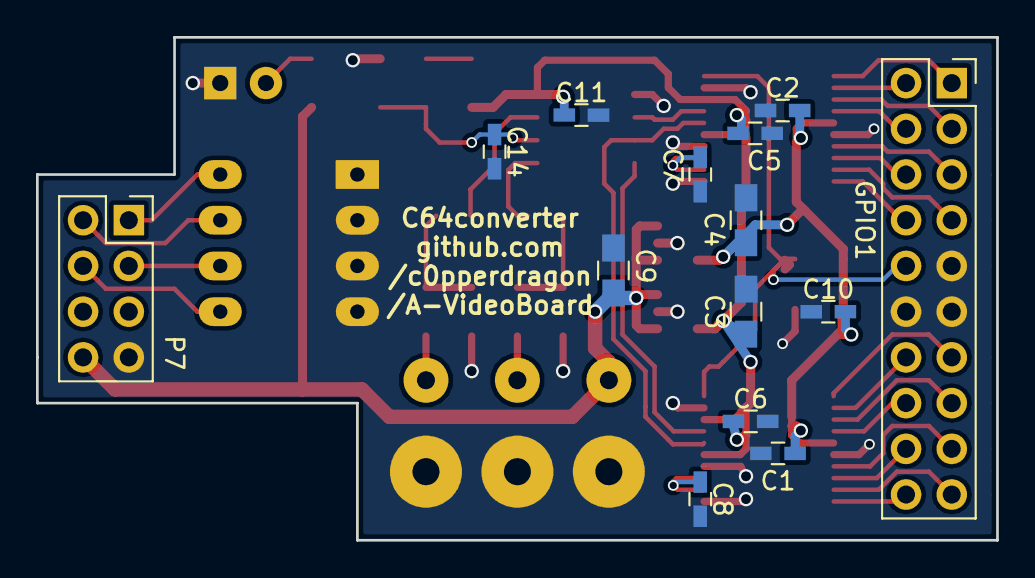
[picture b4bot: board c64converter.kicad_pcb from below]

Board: 2 copper layers, 53.3 x 27.9 mm, 38 parts (14 on the bottom side), 39 nets.

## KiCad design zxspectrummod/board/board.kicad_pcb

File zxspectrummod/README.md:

# ZXSpectrum Mod

Built on the A-Video board, this is a modification usable for the
ZX Spectrum 16K/48K versions (li'l old Speccy) that generates a
YPbPr signal in either 288p or 576p to display on modern displays.

## Motivation

As many home computers of the era, the ZX Spectrum (16K,48K) generates its
video output in the form of a composite signal that was of notoriously
bad quality, even if viewed on an analogue cathode ray tube. With 
modern LCD screens that do some digital preprocessing of the signal,
the result is even more horrible.
Even though the graphics chip (the ULA) outputs the video signal 
as a kind of RGB signal (YUV for these who know their colour formats), this
signal is still very noisy and there is a lot of digital processing
that shows up in the image. 
So this machine was also a good candidate for improvement with
my A-Video board. 

## Building

The construction uses the A-Video board with a small daughter board for shifting
the logic levels from 5V to 3.3V. 
To avoid soldering leads directly to the ULA, I took the
signals from various via points on the board - basically wherever I could
find one. In a few instances I soldered the leads to some other pins of 
various parts - but never to the ULA itself.

You may notice that the mod just fits into the tiny space that is
left in the ZX Spectrum after removing the RF modulator. That is no coincidence. 
The design of the A-Video board itself was totally driven by this exact space
constraint. 

As a side note I want to mention that I have replaced the original 
voltage regulator with its huge heat sink with a modern buck converter 
that generates nearly no heat at all. This will probably reduce the stress on the 
power supply (the original one) as well reduce the temperature in the cramped 
computer case.

## Implementation details

The FPGA chip passively listens to all relevant pins of the ULA and tries to make
sense of what is going on. 
This was not so easy as it may seem, because I was not able to directly extract the pixel
clock. There are no pins on the ULA that would directly provide this. The connection to the 
oscillator quartz is very sensitive to any added load and I could not reliably connect anything
to it without rendering the system unstable. I could also not use the clock output to the CPU 
because the ULA turns this on and off in a totally unpredictable pattern to disable CPU
access to the bus.

I figured out that it is possible to listen to the CAS line which is driven by the ULA to fetch
image data from the memory. All ULA accesses have a very distinct timing pattern and can be well
separated from the accesses that are done on behalf of the CPU. For every 8 pixels that are drawn
on the screen, the ULA fetches two bytes from the same memory row without re-sending the row
address. The FPGA always monitors these bytes and can re-construct the contents of the 
video RAM. 

With a kind of custom PLL-circuit done in the FPGA, I can generate a video output signal that
is in sync with the incoming stream of video data.

## Output

The mod can be used to create three different output formats:
* 288p (default)
* 576p
* 576p with scanlines

Selecting the output can be done by jumper connectors or an external switch:
* Connect GPIO1_18 to GPIO1_17 (or GND): 576p without scanlines
* Connect GPIO1_15 to GPIO1_17 (or GND): 576p with scanlines 

## Images

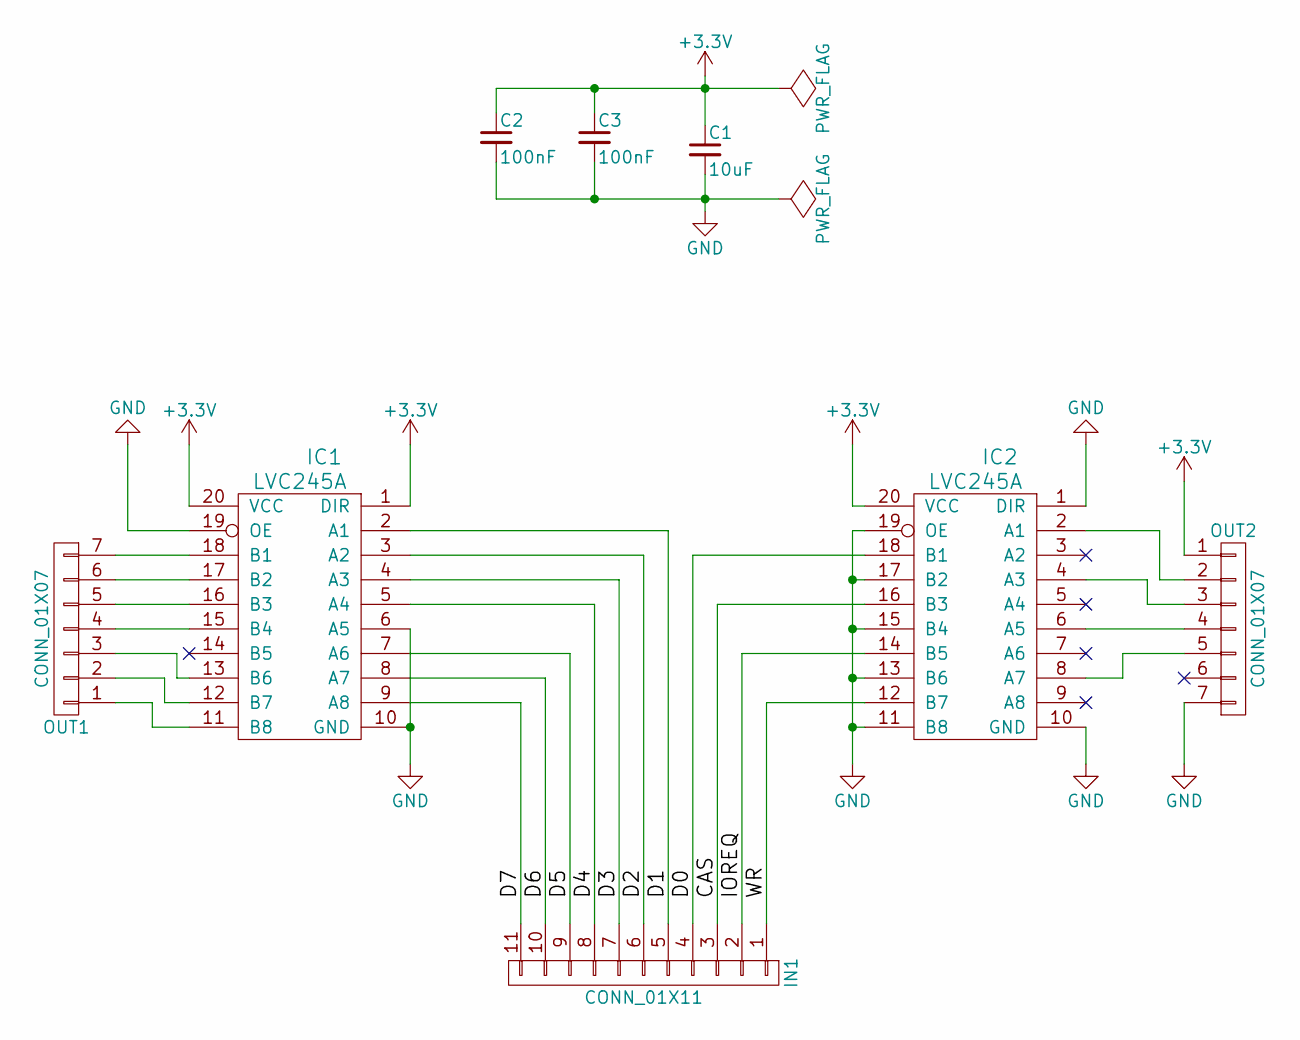
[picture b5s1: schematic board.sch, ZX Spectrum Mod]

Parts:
C1: 10uF; C_0805_HandSoldering
C2, C3: 100nF; C_0603_HandSoldering
IC1, IC2: LVC245A; SOIC-20W_7.5x12.8mm_Pitch1.27mm
IN1: CONN_01X11; Pin_Header_Straight_1x11_Pitch2.54mm
OUT1, OUT2: CONN_01X07; Pin_Header_Straight_1x07_Pitch2.54mm

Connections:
+3V3: C1.1, C2.1, C3.1, IC1.1 (DIR), IC1.20 (VCC), IC2.20 (VCC), OUT2.1
/CAS: IC2.16 (B3), IN1.3
/D0: IC2.18 (B1), IN1.4
/D1: IC1.2 (A1), IN1.5
/D2: IC1.3 (A2), IN1.6
/D3: IC1.4 (A3), IN1.7
/D4: IC1.5 (A4), IN1.8
/D5: IC1.7 (A6), IN1.9
/D6: IC1.8 (A7), IN1.10
/D7: IC1.9 (A8), IN1.11
/IOREQ: IC2.14 (B5), IN1.2
/WR: IC2.12 (B7), IN1.1
GND: C1.2, C2.2, C3.2, IC1.6 (A5), IC1.10 (GND), IC1.19 (OE), IC2.1 (DIR), IC2.10 (GND), IC2.11 (B8), IC2.13 (B6), IC2.15 (B4), IC2.17 (B2), IC2.19 (OE), OUT2.7
unnamed: IC1.11 (B8), OUT1.1
unnamed: IC1.12 (B7), OUT1.2
unnamed: IC1.13 (B6), OUT1.3
unnamed: IC1.15 (B4), OUT1.4
unnamed: IC1.16 (B3), OUT1.5
unnamed: IC1.17 (B2), OUT1.6
unnamed: IC1.18 (B1), OUT1.7
unnamed: IC2.2 (A1), OUT2.2
unnamed: IC2.4 (A3), OUT2.3
unnamed: IC2.6 (A5), OUT2.4
unnamed: IC2.8 (A7), OUT2.5

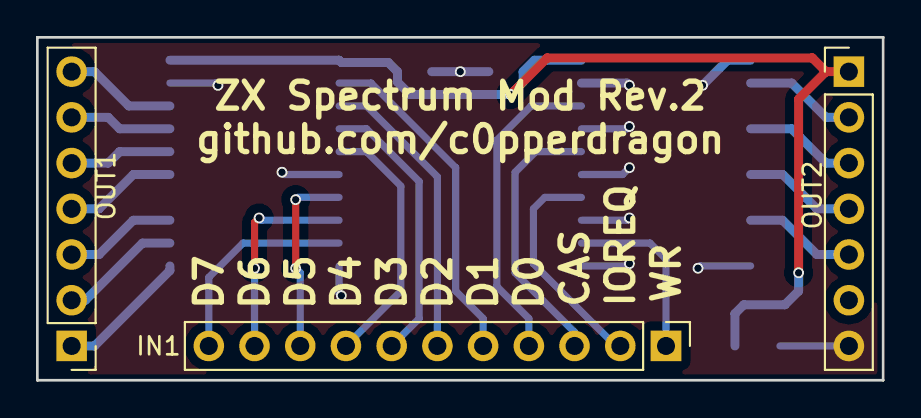
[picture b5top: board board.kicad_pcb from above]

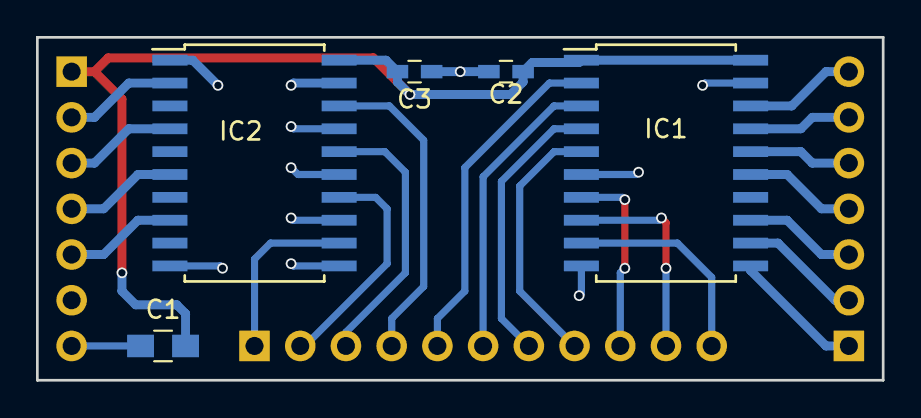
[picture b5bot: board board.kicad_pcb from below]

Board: 2 copper layers, 47.0 x 19.0 mm, 8 parts (5 on the bottom side), 24 nets.
